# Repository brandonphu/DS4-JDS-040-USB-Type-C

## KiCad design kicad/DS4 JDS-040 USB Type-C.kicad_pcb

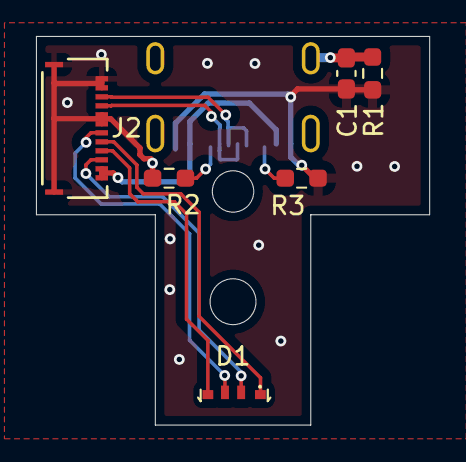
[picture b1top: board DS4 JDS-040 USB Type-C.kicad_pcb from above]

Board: 2 copper layers, 21.8 x 21.6 mm, 7 parts (1 on the bottom side), 11 nets.

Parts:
C1: 4.7nF; C_0603_1608Metric_Pad1.08x0.95mm_HandSolder
D1: FM-3510RGBA-SG
J1: USB4105-GF-A; GCT_USB4105-GF-A
J2: 5034801200; CON_5034801200_MOL
R1: 1M; R_0603_1608Metric_Pad0.98x0.95mm_HandSolder
R2, R3: 5.1K; R_0603_1608Metric_Pad0.98x0.95mm_HandSolder

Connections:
/SHIELD4: C1.1, J1.SH4 (SHIELD4), R1.1
ANODE: D1.2 (A), J2.10
BLUE: D1.4 (BK), J2.9
CC1: J1.A5 (CC1), R2.1
CC2: J1.B5 (CC2), R3.1
GND: C1.2, J1.A1_B12 (GND), J1.B1_A12 (GND), J2.1, J2.2, J2.5, J2.6, J2.P1, J2.P2, R1.2, R2.2, R3.2
GREEN: D1.3 (GK), J2.7
RED: D1.1 (RK), J2.8
USB_D+: J1.A6 (DP1), J1.B6 (DP2), J2.3
USB_D-: J1.A7 (DN1), J1.B7 (DN2), J2.4
VUSB: J1.A4_B9 (VBUS), J1.B4_A9 (VBUS), J2.11, J2.12

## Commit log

2024-12-07 pdf rename
